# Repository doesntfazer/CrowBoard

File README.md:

# Crowboard

 Single Board 34/36 Key Keyboard

Check out [Docs](https://github.com/doesntfazer/CrowBoard/tree/main/Docs) for build instructions

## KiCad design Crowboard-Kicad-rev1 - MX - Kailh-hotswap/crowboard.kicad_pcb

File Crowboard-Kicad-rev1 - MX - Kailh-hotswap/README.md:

# Crowboard Rev1 MX
This board is tested and working

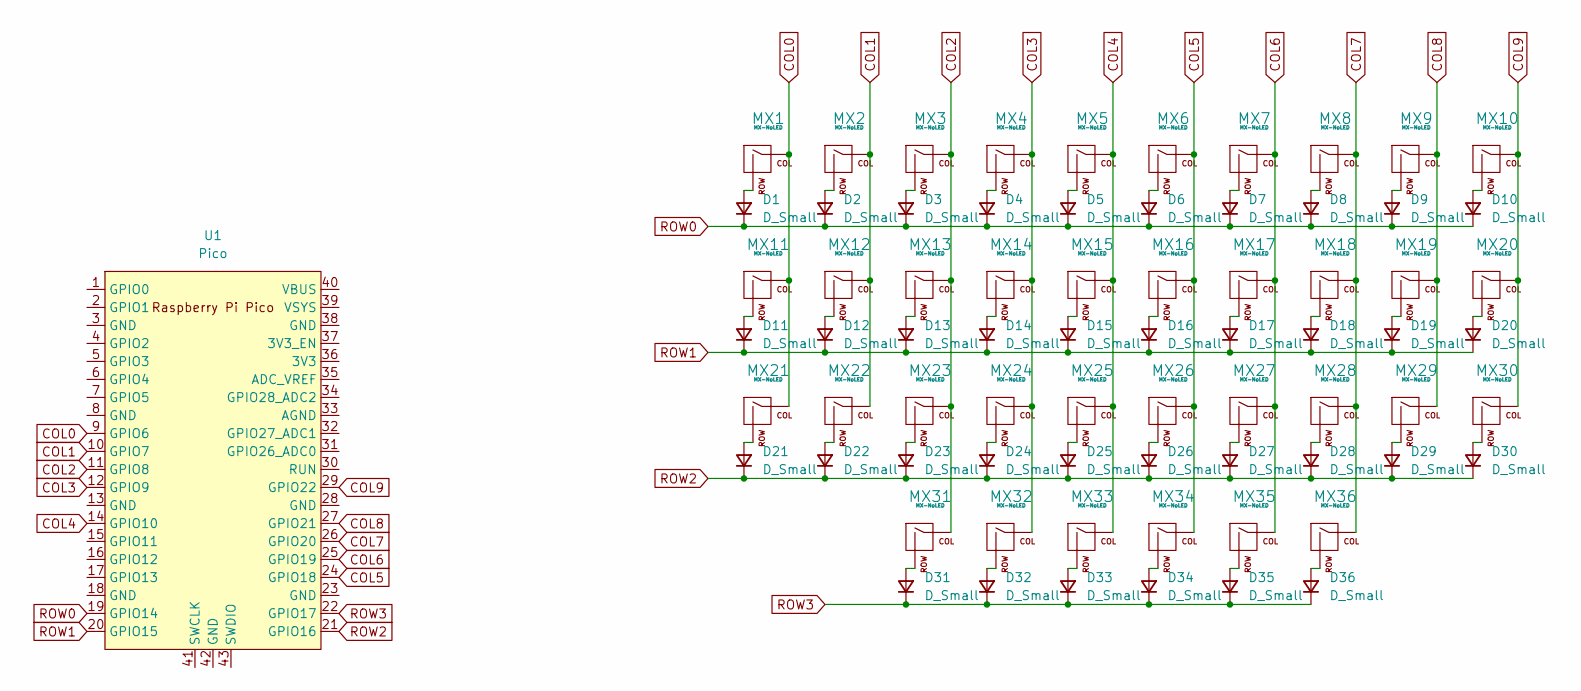
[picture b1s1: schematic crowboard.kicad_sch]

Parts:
D1, D2, D3, D4, D5, D6, D7, D8, D9, D10, D11, D12, D13, D14, D15, D16, D17, D18, D19, D20, D21, D22, D23, D24, D25, D26, D27, D28, D29, D30, D31, D32, D33, D34, D35, D36: D_Small; Diode-Hybrid-Back
MX1, MX2, MX3, MX4, MX5, MX6, MX7, MX8, MX9, MX10, MX11, MX12, MX13, MX14, MX15, MX16, MX17, MX18, MX19, MX20, MX21, MX22, MX23, MX24, MX25, MX26, MX27, MX28, MX29, MX30, MX31, MX32, MX33, MX34, MX35, MX36: MX-NoLED
U1: Pico; RPi_Pico_SMD_TH

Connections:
COL0: MX1.1 (COL), MX11.1 (COL), MX21.1 (COL), U1.9 (GPIO6)
COL1: MX2.1 (COL), MX12.1 (COL), MX22.1 (COL), U1.10 (GPIO7)
COL2: MX3.1 (COL), MX13.1 (COL), MX23.1 (COL), MX31.1 (COL), U1.11 (GPIO8)
COL3: MX4.1 (COL), MX14.1 (COL), MX24.1 (COL), MX32.1 (COL), U1.12 (GPIO9)
COL4: MX5.1 (COL), MX15.1 (COL), MX25.1 (COL), MX33.1 (COL), U1.14 (GPIO10)
COL5: MX6.1 (COL), MX16.1 (COL), MX26.1 (COL), MX34.1 (COL), U1.24 (GPIO18)
COL6: MX7.1 (COL), MX17.1 (COL), MX27.1 (COL), MX35.1 (COL), U1.25 (GPIO19)
COL7: MX8.1 (COL), MX18.1 (COL), MX28.1 (COL), MX36.1 (COL), U1.26 (GPIO20)
COL8: MX9.1 (COL), MX19.1 (COL), MX29.1 (COL), U1.27 (GPIO21)
COL9: MX10.1 (COL), MX20.1 (COL), MX30.1 (COL), U1.29 (GPIO22)
unnamed: D1.2 (A), MX1.2 (ROW)
unnamed: D2.2 (A), MX2.2 (ROW)
unnamed: D3.2 (A), MX3.2 (ROW)
unnamed: D4.2 (A), MX4.2 (ROW)
unnamed: D5.2 (A), MX5.2 (ROW)
unnamed: D6.2 (A), MX6.2 (ROW)
unnamed: D7.2 (A), MX7.2 (ROW)
unnamed: D8.2 (A), MX8.2 (ROW)
unnamed: D9.2 (A), MX9.2 (ROW)
unnamed: D10.2 (A), MX10.2 (ROW)
unnamed: D11.2 (A), MX11.2 (ROW)
unnamed: D12.2 (A), MX12.2 (ROW)
unnamed: D13.2 (A), MX13.2 (ROW)
unnamed: D14.2 (A), MX14.2 (ROW)
unnamed: D15.2 (A), MX15.2 (ROW)
unnamed: D16.2 (A), MX16.2 (ROW)
unnamed: D17.2 (A), MX17.2 (ROW)
unnamed: D18.2 (A), MX18.2 (ROW)
unnamed: D19.2 (A), MX19.2 (ROW)
unnamed: D20.2 (A), MX20.2 (ROW)
unnamed: D21.2 (A), MX21.2 (ROW)
unnamed: D22.2 (A), MX22.2 (ROW)
unnamed: D23.2 (A), MX23.2 (ROW)
unnamed: D24.2 (A), MX24.2 (ROW)
unnamed: D25.2 (A), MX25.2 (ROW)
unnamed: D26.2 (A), MX26.2 (ROW)
unnamed: D27.2 (A), MX27.2 (ROW)
unnamed: D28.2 (A), MX28.2 (ROW)
unnamed: D29.2 (A), MX29.2 (ROW)
unnamed: D30.2 (A), MX30.2 (ROW)
unnamed: D31.2 (A), MX31.2 (ROW)
unnamed: D32.2 (A), MX32.2 (ROW)
unnamed: D33.2 (A), MX33.2 (ROW)
unnamed: D34.2 (A), MX34.2 (ROW)
unnamed: D35.2 (A), MX35.2 (ROW)
unnamed: D36.2 (A), MX36.2 (ROW)
ROW0: D1.1 (K), D2.1 (K), D3.1 (K), D4.1 (K), D5.1 (K), D6.1 (K), D7.1 (K), D8.1 (K), D9.1 (K), D10.1 (K), U1.19 (GPIO14)
ROW1: D11.1 (K), D12.1 (K), D13.1 (K), D14.1 (K), D15.1 (K), D16.1 (K), D17.1 (K), D18.1 (K), D19.1 (K), D20.1 (K), U1.20 (GPIO15)
ROW2: D21.1 (K), D22.1 (K), D23.1 (K), D24.1 (K), D25.1 (K), D26.1 (K), D27.1 (K), D28.1 (K), D29.1 (K), D30.1 (K), U1.21 (GPIO16)
ROW3: D31.1 (K), D32.1 (K), D33.1 (K), D34.1 (K), D35.1 (K), D36.1 (K), U1.22 (GPIO17)

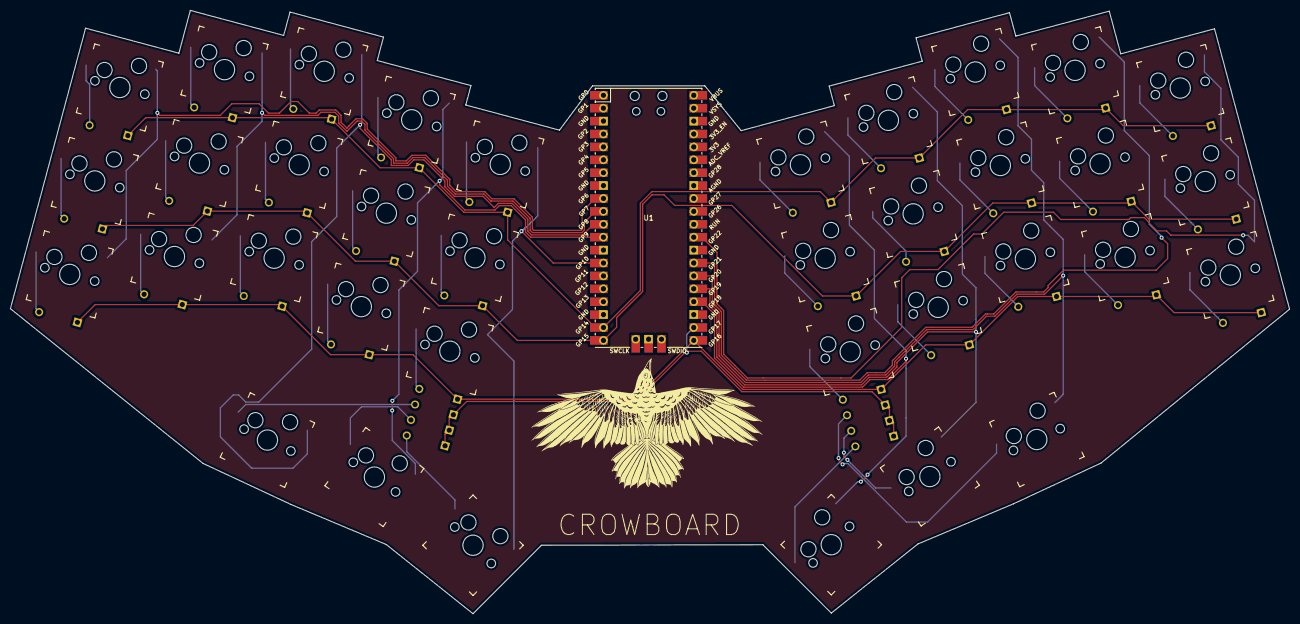
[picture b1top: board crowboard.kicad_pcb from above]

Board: 2 copper layers, 251.9 x 118.8 mm, 73 parts (0 on the bottom side), 50 nets.

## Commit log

2022-04-18 first
2022-04-18 second
2022-04-18 move
2022-04-18 adjustments
2022-04-19 finished
2022-04-19 final
2022-04-19 fix routing
2022-04-20 finish
2022-04-20 rev2
2022-04-20 switch options
2022-04-21 finrev2
2022-04-21 more
2022-04-29 remove unneeded files
2022-04-29 renamed folder
2022-05-02 MX Version
2022-05-02 removed
2022-05-02 move gbr
2022-05-02 mx gerber
2022-05-12 Removed Pimoroni Trackball
2022-05-12 remove backups
2022-05-15 Crowboard Rev 2 MX
2022-05-15 removed backup files
    removed
2022-05-15 fix naming convention
2022-05-15 moved components and pretty
    Better organization of files
2022-05-15 removed 2.1 folder
2022-05-15 docs
2022-05-15 Rename crowboardchoc.md to README.md
2022-05-15 4 encoders
2022-05-16 changes to rev2 mx
2022-05-16 rename rev to rev1 choc
2022-06-01 added case files
2023-02-24 Made a hot-swappable version
    Just for you wusarhu
